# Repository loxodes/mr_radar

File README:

mr_radar
=============

mr_radar is an in development open hardware frequency modulated continuous wave radar.

It is a radar altimeter for remote control quad-rotor helicopters and UAVs.
Eventually, it may be capable of radar imaging.

One of the goals of this project is to be easily reproducible and inexpensive.
All of the microwave components are available online from manufacturers or resellers like DigiKey, Allied Electronics, or Mini-Circuits. I have avoided using expensive components like circulators or SAW delay lines, even though they sound like fun. No chips with exposed pads are used, it is possible to assemble the boards with a soldering iron. All of the printed circuit boards are intended for plain inexpensive FR4 (which means filtering is done using chip filters and lumped elements, not distributed elements) and could be purchased from inexpensive board houses such as seeedstudio or iteadstudio. (I have several spares of most boards, I am willing to mail them out in exchange for postage.)
Signal processing will be done on a STM32F4 microcontroller, the STM32F4-Discovery evaluation board is available for around twenty dollars. 

Several test boards have been created for this project:
- mr_radar_frogpond proved the VCO and preamplifier amplifier layout and schematic.
- mr_radar_platypus contains all the microwave components, and proved the mixer, splitter, and IF amplifier.
- mr_radar_patch_antenna proved the patch antenna layout (it matched ADS simulation!)
- mr_radar_sandbox did not work as expected, the through hole SMA connector did not perform well at 3.4 GHz (but the U.fl did!)
- mr_radar_trolley is an in-progress board with voltage regulators, a VCO driver amplifier, and a USB-USART chip
- mr_radar_sandcastle is an untested board to evaluate an alternate mixer, a power splitter, and a directional coupler.

Some measurements (s-parameters, noise figure measurements) are available in data/ 

Some software has been written for this project:
- stm32f4_dacramp_adcif contains the code for the STM32F4 to generate the VCO control signal and sample the IF, and some python code to grab data off the STM32F4 and test signal processing
- vco_correction is an attempt at a VCO non-linearity correction algorithm. It is untested on hardware (because it requires expensive delay lines)
- compression is an in-progress (class project for a data compression class) to do image compression on the radar images (on the microcontroller)

Board layout is done so using Cadsoft Eagle.
Diagrams are drawn using Dia.
Software is written in Matlab, Python, and C.

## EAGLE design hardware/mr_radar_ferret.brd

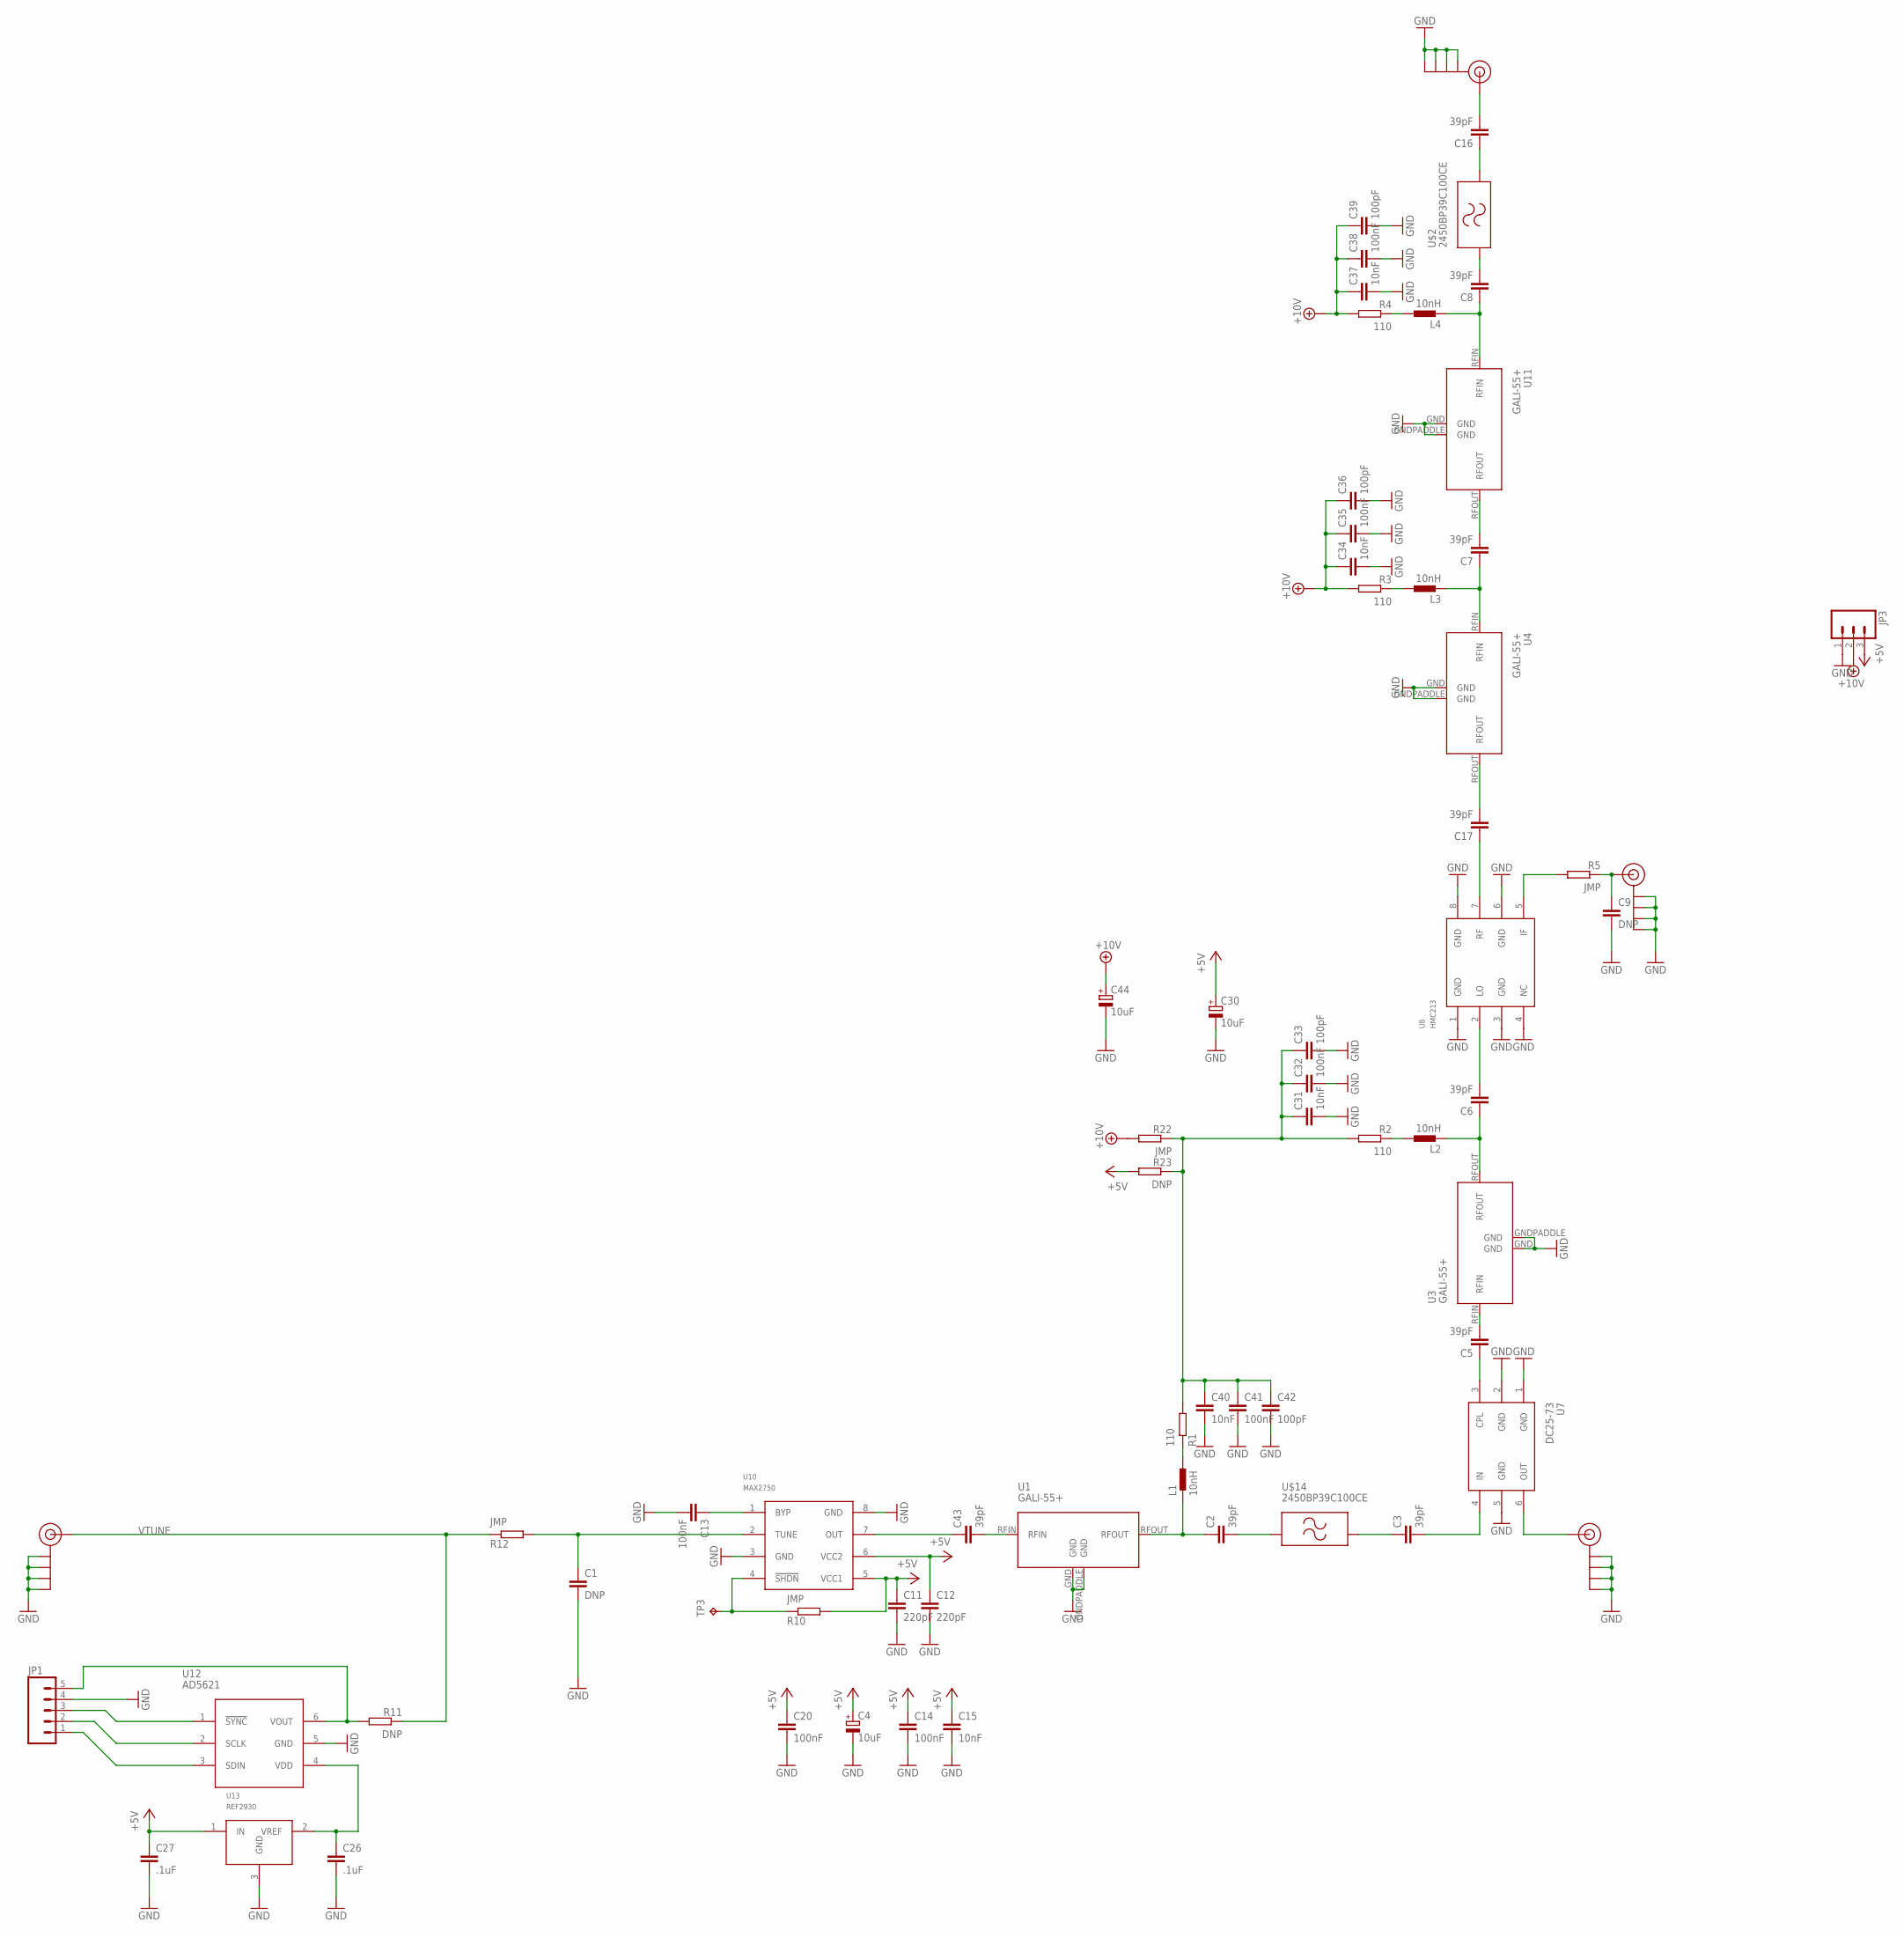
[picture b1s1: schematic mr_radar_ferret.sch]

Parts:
C1, C9: DNP; 0603-CAP
C2, C3, C5, C6, C7, C8, C16, C17, C43: 39pF; 0603-CAP
C4, C30, C44: 10uF; 3216/A
C11, C12: 220pF; 0603-CAP
C13, C14, C20, C32, C35, C38, C41: 100nF; 0603-CAP
C15, C31, C34, C37, C40: 10nF; 0603-CAP
C26, C27: .1uF; 0603-CAP
C33, C36, C39, C42: 100pF; 0603-CAP
J$1, J$2, J$4, J$5: SMA_EDGE; SMA-EDGE
JP1: M05PTH; 1X05
JP3: M03SCREW; SCREWTERMINAL-3.5MM-3
L1, L2, L3, L4: 10nH; 0603-IND
R1, R2, R3, R4: 110; 0603-RES
R5, R10, R12, R22: JMP; 0603-RES
R11, R23: DNP; 0603-RES
TP3: TPTP14SQ; TP14SQ
U1, U3, U4, U11: GALI-55+; SOT89
U7: DC25-73; SOT23-6
U8: HMC213; UMAX8
U10: MAX2750; UMAX8
U12: AD5621; SC70-6L
U13: REF2930; SOT23-3
U$2, U$14: 2450BP39C100CE; 2450BP39C100C

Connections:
+5V: C4.+, C11.P$1 (1), C12.P$1 (1), C14.P$1 (1), C15.P$1 (1), C20.P$1 (1), C27.P$1 (1), C30.+, JP3.3, R10.P$2 (2), R23.P$2 (2), U10.5 (VCC1), U10.6 (VCC2), U13.1 (IN)
+10V: C34.P$1 (1), C35.P$1 (1), C36.P$1 (1), C37.P$1 (1), C38.P$1 (1), C39.P$1 (1), C44.+, JP3.2, R3.P$2 (2), R4.P$2 (2), R22.P$2 (2)
GND: C1.P$2 (2), C4.-, C9.P$2 (2), C11.P$2 (2), C12.P$2 (2), C13.P$2 (2), C14.P$2 (2), C15.P$2 (2), C20.P$2 (2), C26.P$2 (2), C27.P$2 (2), C30.-, C31.P$2 (2), C32.P$2 (2), C33.P$2 (2), C34.P$2 (2), C35.P$2 (2), C36.P$2 (2), C37.P$2 (2), C38.P$2 (2), C39.P$2 (2), C40.P$2 (2), C41.P$2 (2), C42.P$2 (2), C44.-, J$1.GND@0 (GND), J$1.GND@1 (GND), J$1.GND@2 (GND), J$1.GND@3 (GND), J$2.GND@0 (GND), J$2.GND@1 (GND), J$2.GND@2 (GND), J$2.GND@3 (GND), J$4.GND@0 (GND), J$4.GND@1 (GND), J$4.GND@2 (GND), J$4.GND@3 (GND), J$5.GND@0 (GND), J$5.GND@1 (GND), J$5.GND@2 (GND), J$5.GND@3 (GND), JP1.4, JP3.1, U1.GND, U1.GNDPADDLE (GND), U3.GND, U3.GNDPADDLE (GND), U4.GND, U4.GNDPADDLE (GND), U7.1 (GND), U7.2 (GND), U7.5 (GND), U8.1 (GND), U8.3 (GND), U8.4 (NC), U8.6 (GND), U8.8 (GND), U10.3 (GND), U10.8 (GND), U11.GND, U11.GNDPADDLE (GND), U12.5 (GND), U13.3 (GND), U$2.PGND$3 (GND), U$2.PGND$4 (GND), U$14.PGND$3 (GND), U$14.PGND$4 (GND)
unnamed: L1.P$1 (1), R1.P$1 (1)
unnamed: C2.P$1 (1), L1.P$2 (2), U1.RFOUT
unnamed: C2.P$2 (2), U$14.P$2
unnamed: C43.P$2 (2), U1.RFIN
unnamed: C3.P$2 (2), U7.4 (IN)
unnamed: J$2.SIG (SIGNAL), U7.6 (OUT)
unnamed: R10.P$1 (1), TP3.TP, U10.4 (!SHDN)
unnamed: C17.P$2 (2), U4.RFOUT
unnamed: C5.P$1 (1), U7.3 (CPL)
unnamed: C5.P$2 (2), U3.RFIN
unnamed: L2.P$1 (1), R2.P$1 (1)
unnamed: C6.P$1 (1), L2.P$2 (2), U3.RFOUT
unnamed: C6.P$2 (2), U8.2 (LO)
unnamed: C17.P$1 (1), U8.7 (RF)
unnamed: L4.P$1 (1), R4.P$1 (1)
unnamed: L3.P$1 (1), R3.P$1 (1)
unnamed: C7.P$1 (1), L3.P$2 (2), U4.RFIN
unnamed: C8.P$1 (1), L4.P$2 (2), U11.RFIN
unnamed: C8.P$2 (2), U$2.P$2
unnamed: R5.P$2 (2), U8.5 (IF)
unnamed: C7.P$2 (2), U11.RFOUT
unnamed: C13.P$1 (1), U10.1 (BYP)
unnamed: C1.P$1 (1), R12.P$2 (2), U10.2 (TUNE)
unnamed: C16.P$2 (2), J$1.SIG (SIGNAL)
unnamed: C16.P$1 (1), U$2.P$1
unnamed: C3.P$1 (1), U$14.P$1
unnamed: C9.P$1 (1), J$5.SIG (SIGNAL), R5.P$1 (1)
unnamed: C26.P$1 (1), U12.4 (VDD), U13.2 (VREF)
unnamed: JP1.1, U12.3 (SDIN)
unnamed: JP1.2, U12.2 (SCLK)
unnamed: JP1.3, U12.1 (!SYNC)
unnamed: C31.P$1 (1), C32.P$1 (1), C33.P$1 (1), C40.P$1 (1), C41.P$1 (1), C42.P$1 (1), R1.P$2 (2), R2.P$2 (2), R22.P$1 (1), R23.P$1 (1)
unnamed: C43.P$1 (1), U10.7 (OUT)
unnamed: JP1.5, R11.P$2 (2), U12.6 (VOUT)
VTUNE: J$4.SIG (SIGNAL), R11.P$1 (1), R12.P$1 (1)

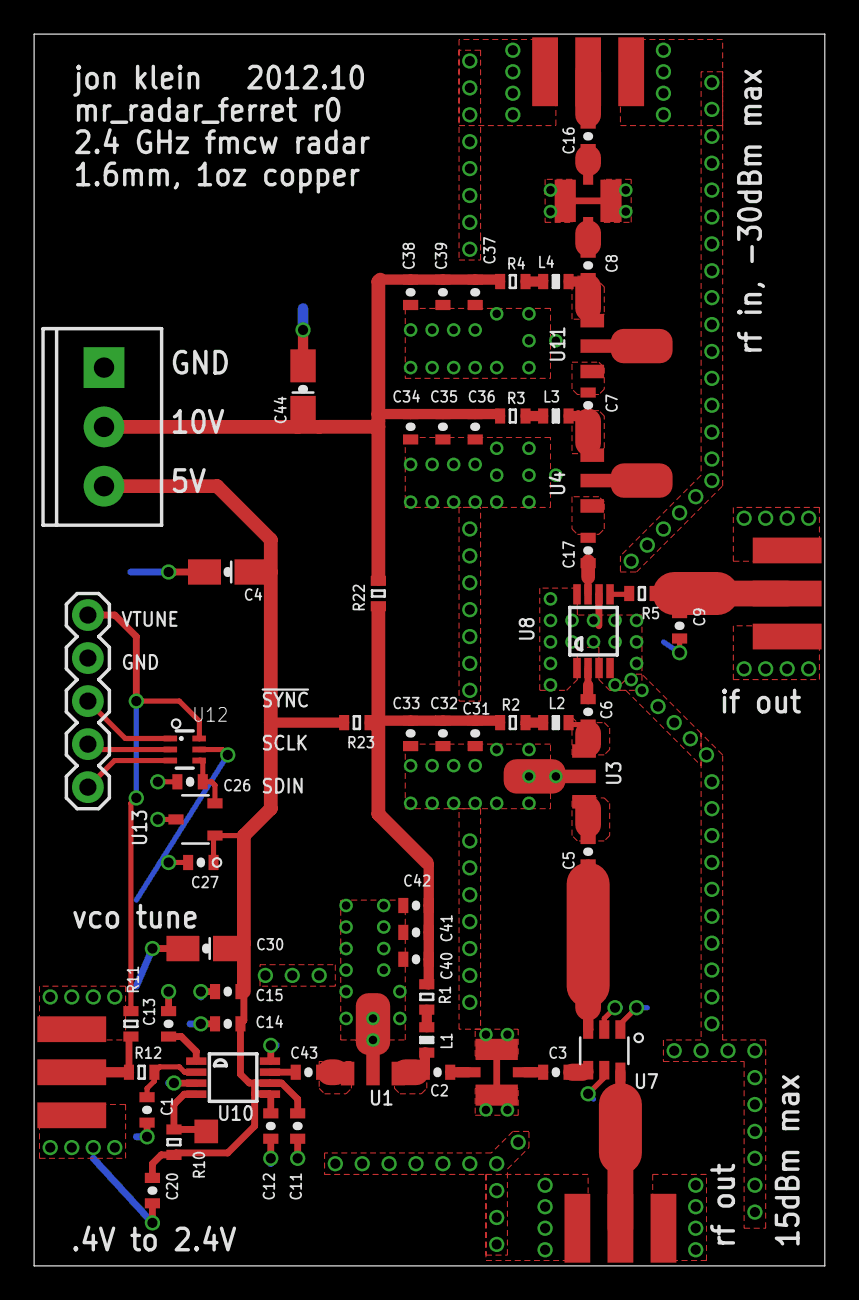
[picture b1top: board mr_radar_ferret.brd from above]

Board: 2 copper layers, 46.7 x 72.7 mm, 66 parts (0 on the bottom side), 38 nets.

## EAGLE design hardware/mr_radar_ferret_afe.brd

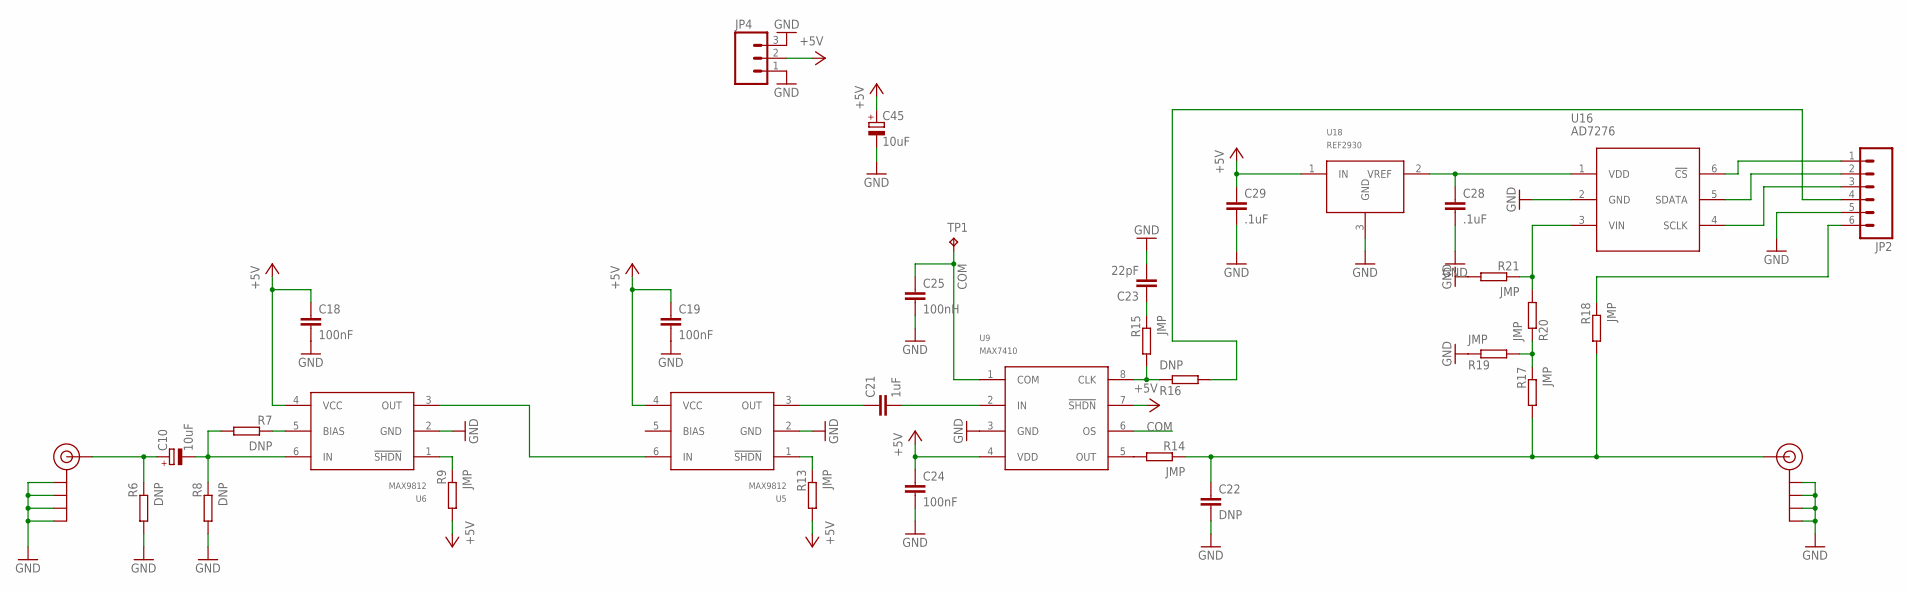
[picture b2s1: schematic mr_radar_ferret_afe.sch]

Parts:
C10, C45: 10uF; 3216/A
C18, C19, C24: 100nF; 0603-CAP
C21: 1uF; 0603-CAP
C22: DNP; 0603-CAP
C23: 22pF; 0603-CAP
C25: 100nH; 0603-CAP
C28, C29: .1uF; 0603-CAP
J$3, J$6: SMA_EDGE; SMA-EDGE
JP2: M06SIP; 1X06
JP4: M03SCREW; SCREWTERMINAL-3.5MM-3
R6, R7, R8, R16: DNP; 0603-RES
R9, R13, R14, R15, R17, R18, R19, R20, R21: JMP; 0603-RES
TP1: TPTP14SQ; TP14SQ
U5, U6: MAX9812; SC70-6
U9: MAX7410; UMAX8
U16: AD7276; SOT23-6
U18: REF2930; SOT23-3

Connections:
+5V: C18.P$1 (1), C19.P$1 (1), C24.P$1 (1), C29.P$1 (1), C45.+, JP4.2, R9.P$2 (2), R13.P$2 (2), U5.4 (VCC), U6.4 (VCC), U9.4 (VDD), U9.7 (!SHDN), U18.1 (IN)
COM: C25.P$1 (1), TP1.TP, U9.1 (COM), U9.6 (OS)
GND: C18.P$2 (2), C19.P$2 (2), C22.P$2 (2), C23.P$2 (2), C24.P$2 (2), C25.P$2 (2), C28.P$2 (2), C29.P$2 (2), C45.-, J$3.GND@0 (GND), J$3.GND@1 (GND), J$3.GND@2 (GND), J$3.GND@3 (GND), J$6.GND@0 (GND), J$6.GND@1 (GND), J$6.GND@2 (GND), J$6.GND@3 (GND), JP2.5, JP4.1, JP4.3, R6.P$2 (2), R8.P$2 (2), R19.P$1 (1), R21.P$2 (2), U5.2 (GND), U6.2 (GND), U9.3 (GND), U16.2 (GND), U18.3 (GND)
unnamed: C10.-, R7.P$2 (2), R8.P$1 (1), U6.6 (IN)
unnamed: U5.6 (IN), U6.3 (OUT)
unnamed: C10.+, J$6.SIG (SIGNAL), R6.P$1 (1)
unnamed: JP2.4, R16.P$2 (2)
unnamed: R9.P$1 (1), U6.1 (!SHDN)
unnamed: R13.P$1 (1), U5.1 (!SHDN)
unnamed: C21.P$1 (1), U5.3 (OUT)
unnamed: C21.P$2 (2), U9.2 (IN)
unnamed: C22.P$1 (1), J$3.SIG (SIGNAL), R14.P$1 (1), R17.P$2 (2), R18.P$2 (2)
unnamed: R14.P$2 (2), U9.5 (OUT)
unnamed: R15.P$2 (2), R16.P$1 (1), U9.8 (CLK)
unnamed: C23.P$1 (1), R15.P$1 (1)
unnamed: R7.P$1 (1), U6.5 (BIAS)
unnamed: JP2.3, U16.4 (SCLK)
unnamed: JP2.1, U16.6 (!CS)
unnamed: JP2.2, U16.5 (SDATA)
unnamed: C28.P$1 (1), U16.1 (VDD), U18.2 (VREF)
unnamed: JP2.6, R18.P$1 (1)
unnamed: R17.P$1 (1), R19.P$2 (2), R20.P$1 (1)
unnamed: R20.P$2 (2), R21.P$1 (1), U16.3 (VIN)

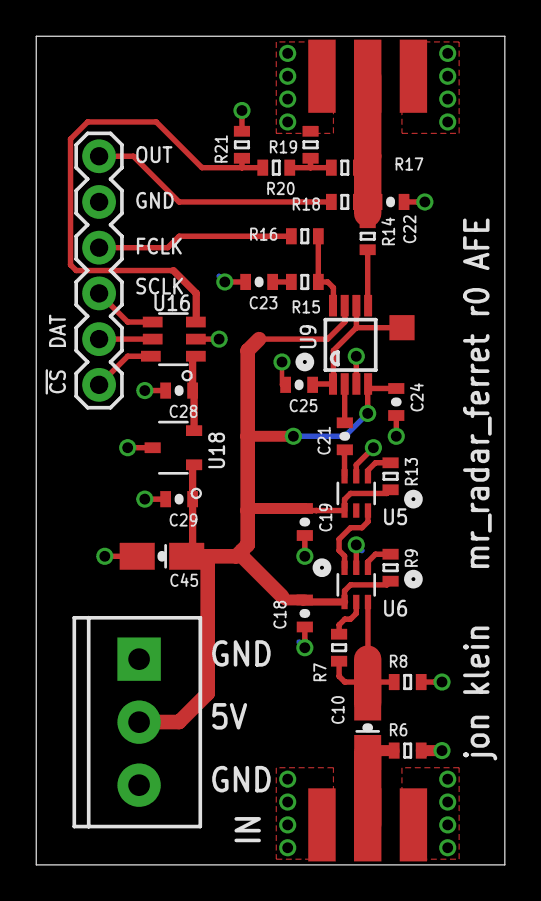
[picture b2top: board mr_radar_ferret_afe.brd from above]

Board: 2 copper layers, 26.0 x 46.0 mm, 34 parts (0 on the bottom side), 23 nets.

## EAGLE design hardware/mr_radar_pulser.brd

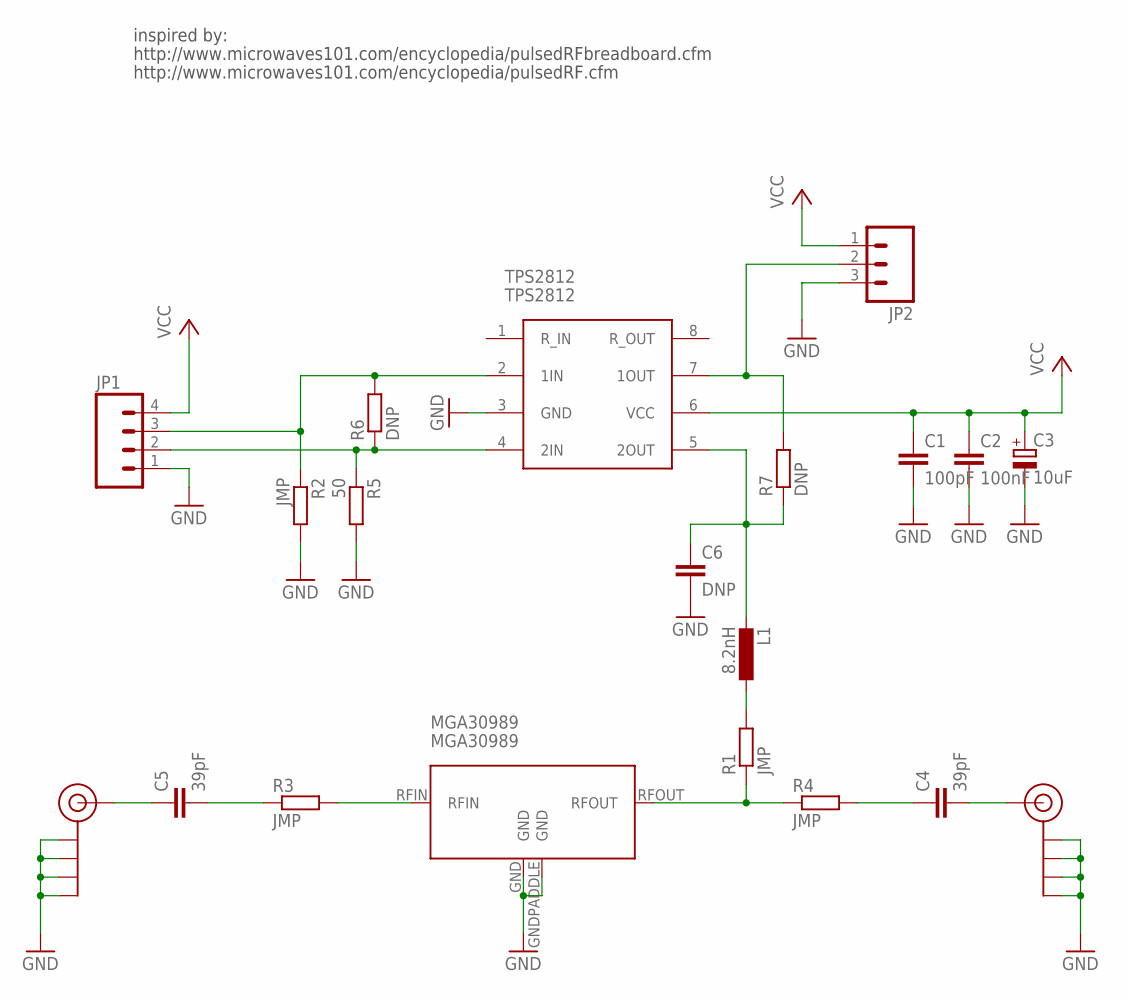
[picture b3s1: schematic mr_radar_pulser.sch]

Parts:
C1: 100pF; C0603
C2: 100nF; C0603
C3: 10uF; CT3216
C4, C5: 39pF; C0402
C6: DNP; C0603
J$1, J$2: SMA_EDGE; SMA-EDGE
JP1: M04PTH; 1X04
JP2: M03PTH; 1X03
L1: 8.2nH; 0603-IND
MGA30989: MGA30989; SOT89
R1, R2: JMP; R0603
R3, R4: JMP; R0402
R5: 50; R0603
R6, R7: DNP; R0603
TPS2812: TPS2812; SO8

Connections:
GND: C1.2, C2.2, C3.-, C6.2, J$1.GND@0 (GND), J$1.GND@1 (GND), J$1.GND@2 (GND), J$1.GND@3 (GND), J$2.GND@0 (GND), J$2.GND@1 (GND), J$2.GND@2 (GND), J$2.GND@3 (GND), JP1.1, JP2.3, MGA30989.GND, MGA30989.GNDPADDLE (GND), R2.2, R5.2, TPS2812.3 (GND)
unnamed: C5.1, J$1.SIG (SIGNAL)
unnamed: C4.1, R4.2
unnamed: MGA30989.RFOUT, R1.1, R4.1
unnamed: C4.2, J$2.SIG (SIGNAL)
unnamed: L1.P$1 (1), R1.2
unnamed: C6.1, L1.P$2 (2), R7.1, TPS2812.5 (2OUT)
unnamed: JP1.3, R2.1, R6.2, TPS2812.2 (1IN)
unnamed: JP1.2, R5.1, R6.1, TPS2812.4 (2IN)
unnamed: JP2.2, R7.2, TPS2812.7 (1OUT)
unnamed: C5.2, R3.1
unnamed: MGA30989.RFIN, R3.2
VCC: C1.1, C2.1, C3.+, JP1.4, JP2.1, TPS2812.6 (VCC)

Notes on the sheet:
http://www.microwaves101.com/encyclopedia/pulsedRF.cfm
http://www.microwaves101.com/encyclopedia/pulsedRFbreadboard.cfm
inspired by:

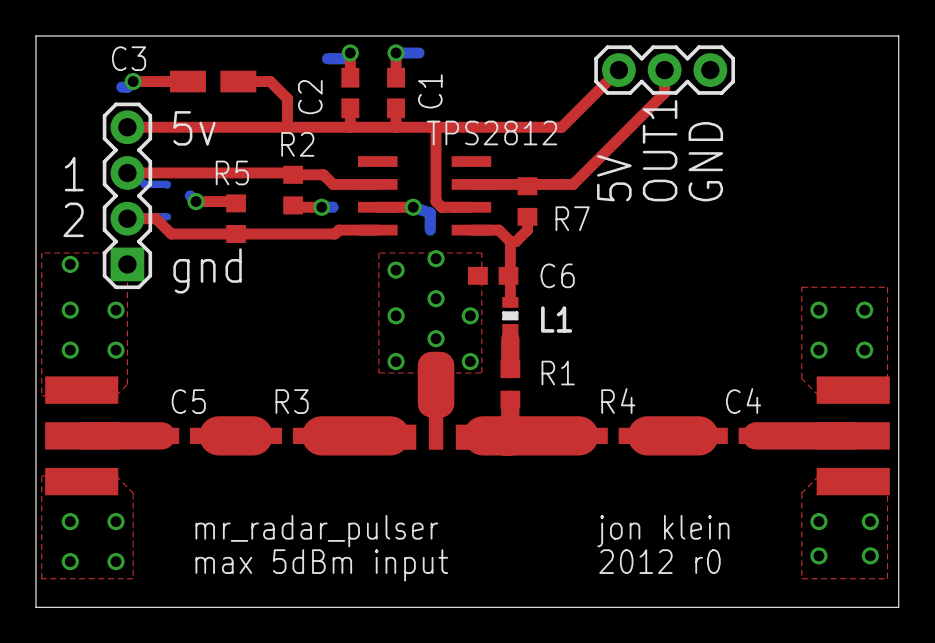
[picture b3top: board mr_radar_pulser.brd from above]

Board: 2 copper layers, 47.9 x 31.7 mm, 20 parts (1 on the bottom side), 13 nets.

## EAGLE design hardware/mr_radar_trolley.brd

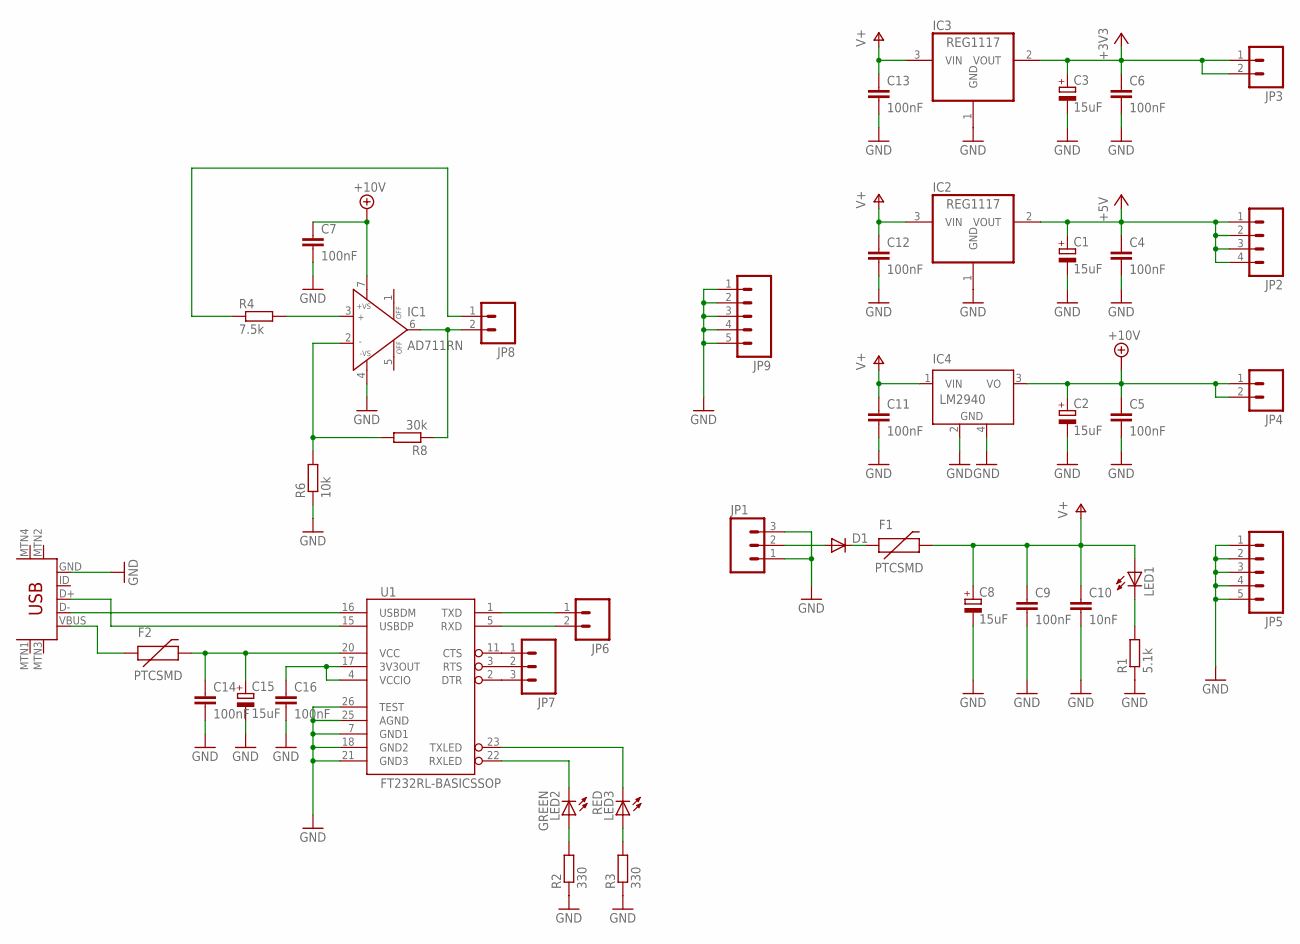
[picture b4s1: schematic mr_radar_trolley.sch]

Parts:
C1, C2, C3, C8, C15: 15uF; B/3528-21R
C4, C5, C6, C7, C9, C11, C12, C13, C14, C16: 100nF; C0603
C10: 10nF; C0603
D1: DIODE-SMC; SMC
F1, F2: PTCSMD; PTC-1206
IC1: AD711RN; SO8
IC2, IC3: REG1117; SOT223
IC4: LM2940; SOT223
JP1: M03SCREW; SCREWTERMINAL-3.5MM-3
JP2: M04LOCK; 1X04_LOCK
JP3, JP4, JP6, JP8: M02PTH; 1X02
JP5, JP9: M05LOCK; 1X05_LOCK
JP7: M03PTH; 1X03
LED1: LEDCHIPLED_1206; CHIPLED_1206
LED2: GREEN; CHIPLED_1206
LED3: RED; CHIPLED_1206
R1: 5.1k; R0603
R2, R3: 330; M0805
R4: 7.5k; R0603
R6: 10k; R0603
R8: 30k; R0603
U1: FT232RL-BASICSSOP; SSOP28DB
U$1: USB-MINIB-5PIN; USB-MINIB

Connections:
+3V3: C3.+, C6.1, IC3.2 (VOUT), JP3.1, JP3.2
+5V: C1.+, C4.1, IC2.2 (VOUT), JP2.1, JP2.2, JP2.3, JP2.4
+10V: C2.+, C5.1, C7.1, IC1.7 (+VS), IC4.3 (VO), JP4.1, JP4.2
GND: C1.-, C2.-, C3.-, C4.2, C5.2, C6.2, C7.2, C8.-, C9.2, C10.2, C11.2, C12.2, C13.2, C14.2, C15.-, C16.2, IC1.4 (-VS), IC2.1 (GND), IC3.1 (GND), IC4.2 (GND), IC4.4 (GND), JP1.1, JP1.3, JP5.1, JP5.2, JP5.3, JP5.4, JP5.5, JP9.1, JP9.2, JP9.3, JP9.4, JP9.5, R1.1, R2.1, R3.1, R6.1, U1.7 (GND1), U1.18 (GND2), U1.21 (GND3), U1.25 (AGND), U1.26 (TEST), U$1.GND
unnamed: D1.C, F1.1
unnamed: D1.A, JP1.2
unnamed: LED1.C, R1.2
unnamed: F2.1, U$1.VBUS
unnamed: U1.16 (USBDM), U$1.D-
unnamed: U1.15 (USBDP), U$1.D+
unnamed: C16.1, U1.4 (VCCIO), U1.17 (3V3OUT)
unnamed: JP6.1, U1.1 (TXD)
unnamed: JP6.2, U1.5 (RXD)
unnamed: C14.1, C15.+, F2.2, U1.20 (VCC)
unnamed: LED3.C, U1.23 (TXLED)
unnamed: LED2.C, U1.22 (RXLED)
unnamed: JP7.1, U1.11 (CTS)
unnamed: JP7.2, U1.3 (RTS)
unnamed: JP7.3, U1.2 (DTR)
unnamed: IC1.2 (IN-), R6.2, R8.2
unnamed: IC1.6 (OUT), JP8.2, R8.1
unnamed: JP8.1, R4.1
unnamed: IC1.3 (IN+), R4.2
V+: C8.+, C9.1, C10.1, C11.1, C12.1, C13.1, F1.2, IC2.3 (VIN), IC3.3 (VIN), IC4.1 (VIN), LED1.A
V+1: LED2.A, R2.2
V+2: LED3.A, R3.2

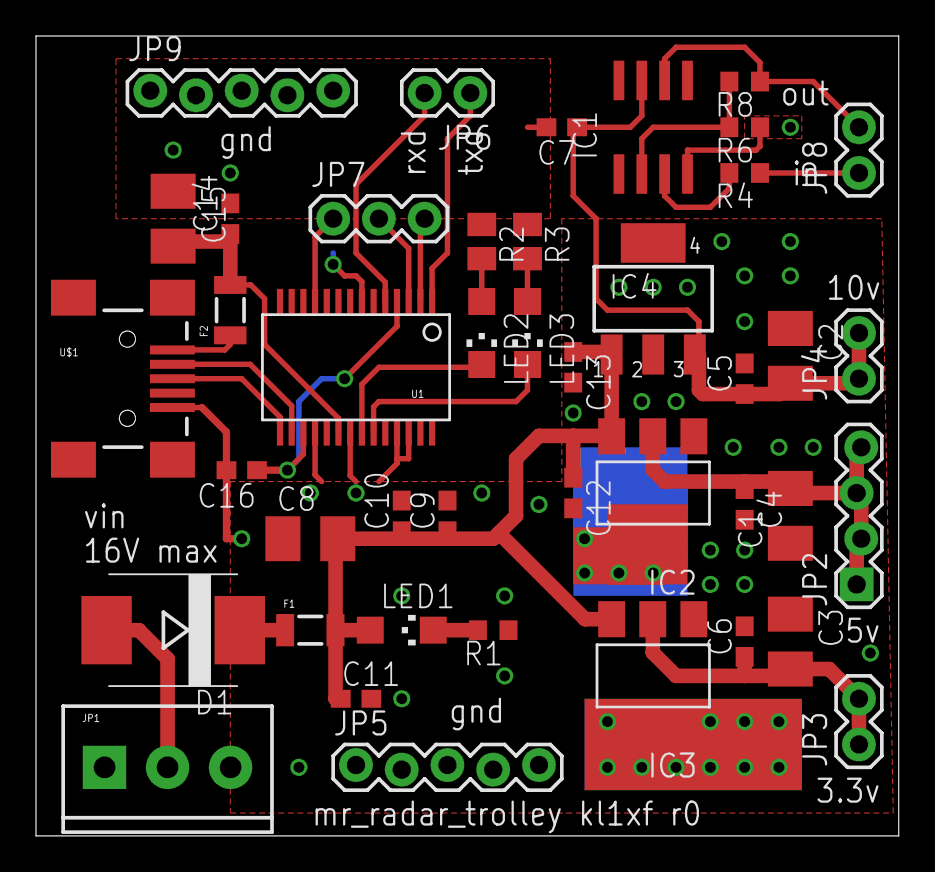
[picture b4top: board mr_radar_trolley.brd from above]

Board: 2 copper layers, 47.9 x 44.4 mm, 43 parts (0 on the bottom side), 26 nets.

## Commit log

2011-09-15 added eagle library with vco, balun, and quad demod
2011-09-15 added warning to readme.
2011-09-15 rough block diagram schematic of mr radar
2011-09-16 added variable gain amplifier to mr_radar library, started amplfier setup. I'll need to make a breakout board for the amp to figure out input/output matching..
2011-09-16 draft of trl cal/amplifier/antenna test board
2011-09-16 removed temp files
2011-09-16 added vco to test board
2011-09-16 fixed some drc errors: removed overlapping drills and increased to 6mil minimum spacing where possible
2011-09-16 fixed soldermask errors, added more via staples
2011-09-17 added r0 gerbers for mr radar sandbox, boards should arrive in a few weeks
2011-09-17 added directional coupler to library
2011-09-17 finished quad demod schematic, added antialiasing filter
2011-09-18 added headers vtune, I&Q outputs, supply voltage
2011-09-18 started on sandcastle - coupler, antialiasingfilter, baseband amplifier, and balun test board (maybe mixer too)
2011-09-19 removed antialiasing filter, started on layout
2011-09-19 layout of amplifier
2011-09-20 finished component placement and initial layout of sandcastle
2011-09-23 finished sandcastle layout
2011-10-18 started fmcw MATLAB simulation for vco nonlinearity correction
2011-10-18 added visualization of output
2011-10-19 added test file
2011-10-19 fixed mixer filter, added comments
2011-10-21 added fft output visualization
2011-10-27 added frogpond, 31mil routed fr4 edge launch sma connector amplifier and vco test board
2011-11-01 changed variable names to reflect proper domains..
2011-11-16 added minicircuits smd mixer and splitter
2011-11-16 added mixer/amp/splitter test board
2011-11-16 added messy broken LO output amplifier
2011-11-16 added u.FL testpoints on mixer and splitter, placed all components except LO driver amp
2011-11-16 simple analytic version of first few steps of algoritm working..
2011-11-16 placed lo driver
2011-11-17 layout of rx and lo amp
2011-11-17 partial layout of tx path
2011-11-17 finished first pass of layout. proper stiching vias and optimization remain..
2011-11-17 unfurled layout to larger board
2011-11-18 top ground planes finished
2011-11-24 added heavily via'ed platypus test board
2011-12-02 fixed then broke vco phase noise correction
2011-12-05 phase error detection in matlab simulation sorta works, added ramp vco error model
2011-12-07 properly finding phase errror in vco correction with reasonable assumptions. ~order of magnitude resolution increase for gaussian phase noise model
2011-12-07 updated variable name to reflect sane reality
2011-12-07 updated comments
2011-12-12 cleaned up vco simulation code
2011-12-23 updated layout of radar
2011-12-23 removed temp files..
2012-02-01 mr radar platypus test board ready for manufacturing
2012-02-01 removed some intermediate files
2012-02-04 added patch ~3.4GHz patch antenna (to be milled on campus)
2012-02-05 added component values to schematic, added silkscreen layer
2012-02-06 increased size of u.fl test point jumpers. attached gerbers of r0, sent for manufacturing
2012-02-16 added measured s2p of patch antenna (matches simulation! http://kl1xf.org/1329427704.png), now to optimize it..
2012-02-27 vna and spectrum anayzer measurements of mr_radar_platypus. it works
2012-03-07 added if amp and antialiasing filter values and LTSpice simulation, changed package sizes for rx amp decoupling capacitors, updated silkscreen with proper supply voltages
2012-03-11 added work in progress stm32f4 ramp generator/adc
2012-03-11 added python script to visualize radar output
2012-03-11 improved python/stm serial sync, fixed problems with repeated conversions
2012-03-11 added control of radar samples over serial port
2012-03-12 added bus pirate support to adc_grab (much faster sample uploading..)
2012-03-13 added mr_radar_trolley, voltage regulator/usb to usart/vco driver amplifier board
2012-03-13 finished component placement draft on mr_radar_trolley
2012-03-13 added attempt at clutter removal
2012-03-13 finished mr_radar_trolley layout
2012-03-13 fixed README formatting
2012-03-13 gave README .md extention, maybe this will work..
2012-03-14 fixes to ft232rl layout and schematic, cleanup of silkscreen layer, sent for manufacturing
2012-03-15 added picture of mr_radar_platypus
2012-03-15 updated readme markdown syntax (maybe the image works now?)
2012-03-15 fixed link to image in README.md
2012-03-15 started work on data compression project, added code to read, display, and calculate the entropy of SRTM files
2012-03-20 added pulsed rf source test board
2012-03-20 finished silkscreen layer on mr_radar_pulser
2012-03-22 added LT5534 to library, mr_radar_pulser ready for manufacturing
2012-03-23 added ad4350 and adl5375 to eagle library
2012-03-26 added patch antenna (WLP.2450.25.4.A.02) to library, mr_radar_pulser sent for manufacturing
2012-04-16 added incomplete and untested JPEG-LS encoder
2012-04-16 RLE mode, updated README
2012-04-27 more work on JPEG-LS encoder, still incomplete
2012-04-27 JPEG-LS now runs, missing limited length golomb codes and probably other features
2012-04-28 more work on jpeg_ls, still almost certainly broken
2012-04-29 fixed bugs in limiting golomb codes and more, still broken
2012-04-29 fixed bugs with contex pixels
2012-04-29 fixed some bugs in run mode, still broken..
2012-04-29 fixed more run mode bugs..
2012-04-29 fixed bug with quantization
2012-04-29 removed some debugging code
2012-05-01 added (broken?) lossy JPEG-LS mode
2012-10-03 started work on mr_radar_ferret, and redesigned FMCW front end for 2.4 GHz with an integrated VCO, DAC, and ADC
2012-10-03 component placement complete on ferret, layout partially complete. silkscreen cleanup and amplifier grounds remain
2012-10-03 split adc front-end to another board, changed microstrip for 1.6mm thick board
2012-10-04 mr_radar_ferret r0, sent for manufacturing
2012-10-26 currently tested ferret r0, fixing a few bugs for the next revision, board layout of ferret now incomplete. isolation is much better than in platypus, but it is still a problem
2014-06-13 removed abandoned boards, added latest revision
2014-06-13 updated readme..

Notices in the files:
parts and their libraries:
SparkFun-Connectors: Licensing: CC v3.0 Share-Alike You are welcome to use this library for commercial purposes.
